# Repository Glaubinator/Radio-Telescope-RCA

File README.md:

# Radio-Telescope-RCA
Radio Telescope System for 1 GHz to 2 GHz Operation

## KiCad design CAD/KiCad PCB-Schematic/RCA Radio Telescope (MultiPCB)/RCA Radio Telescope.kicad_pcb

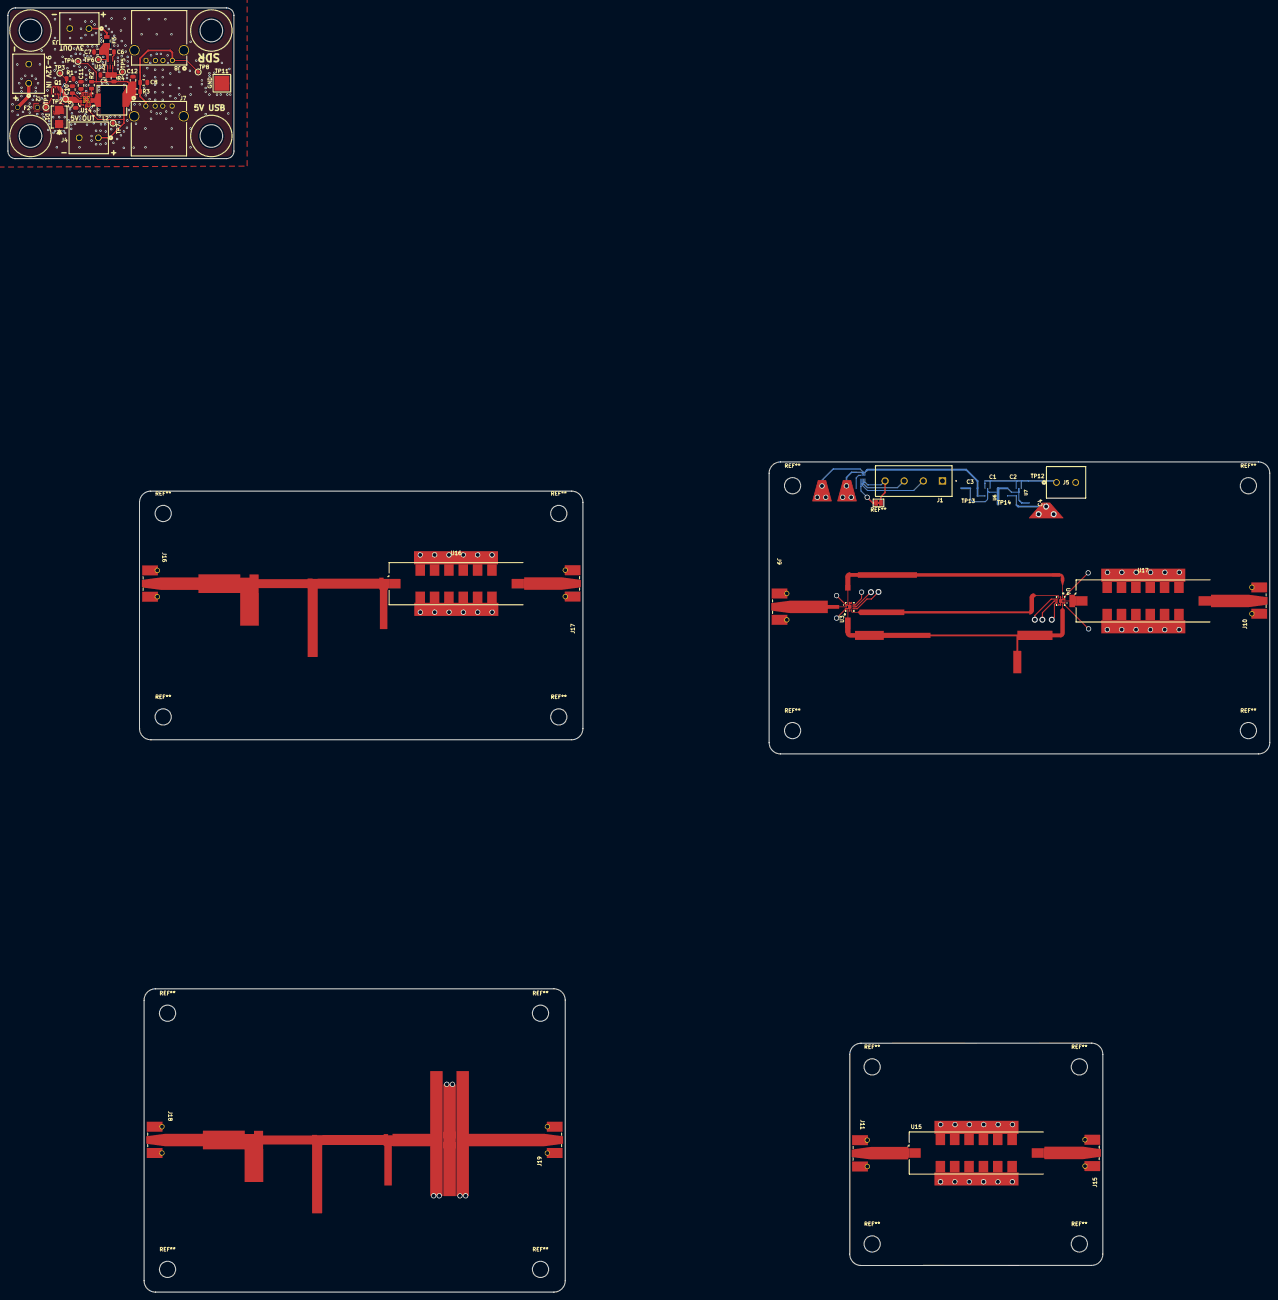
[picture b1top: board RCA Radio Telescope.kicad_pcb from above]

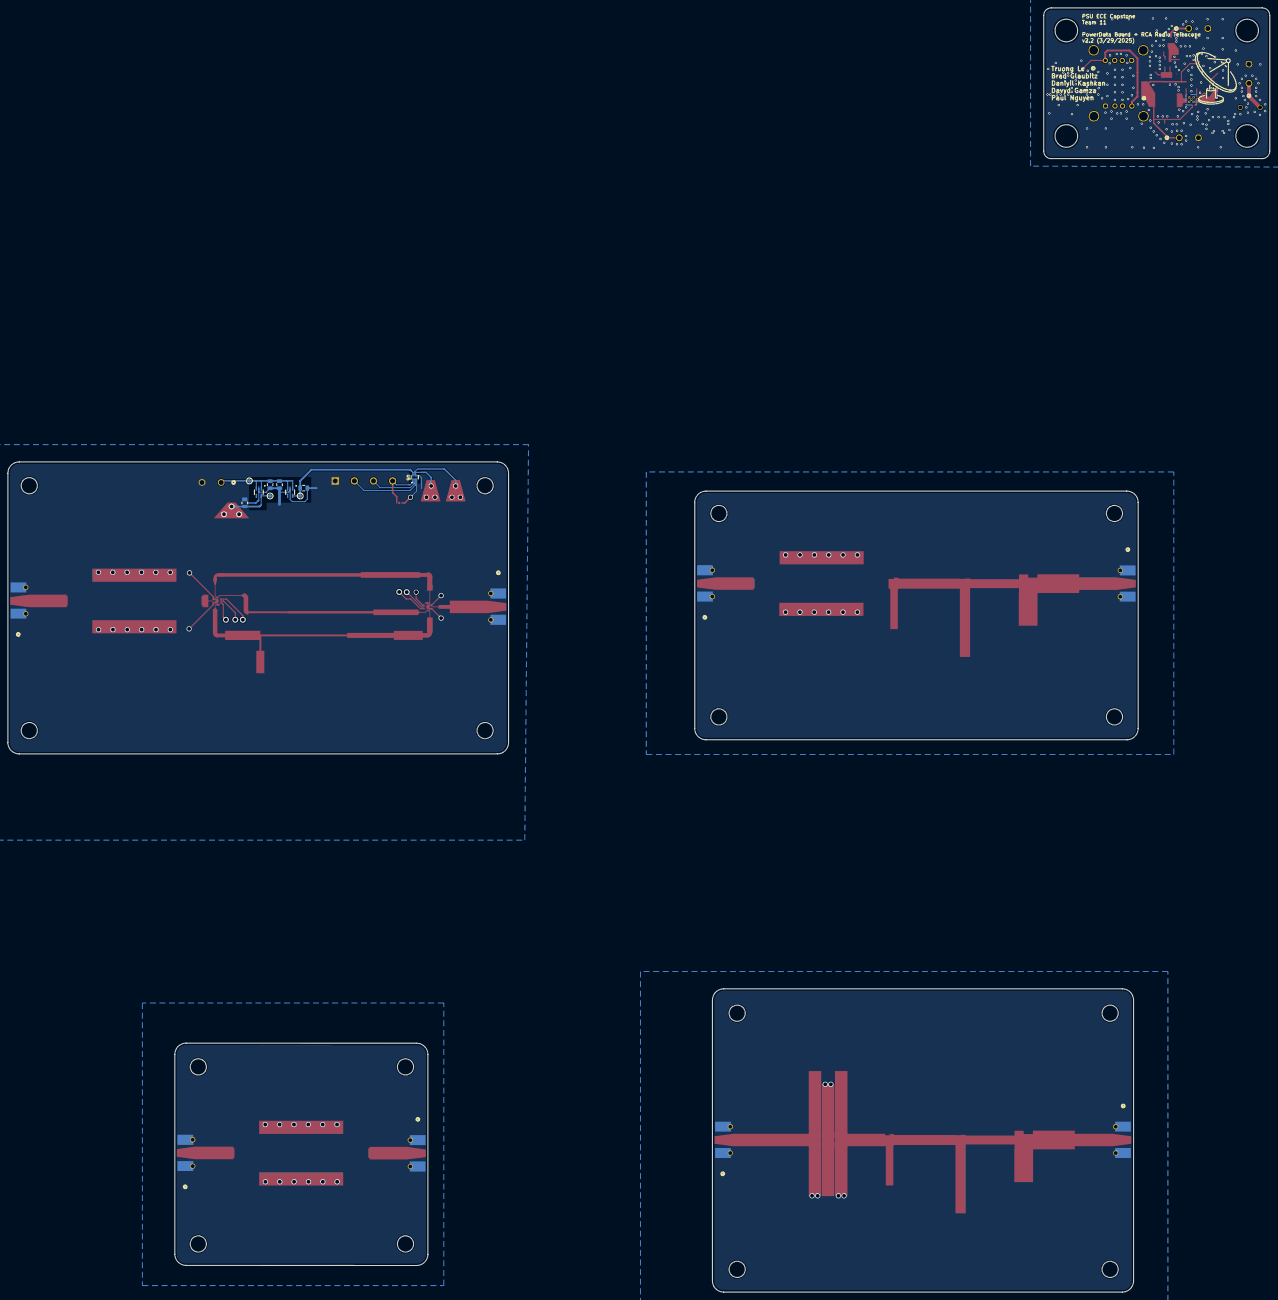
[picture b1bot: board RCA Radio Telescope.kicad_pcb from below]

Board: 2 copper layers, 335.0 x 340.9 mm, 63 parts (10 on the bottom side), 36 nets.

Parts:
C1, C2, C3, C4, C5, C7: 1 uF; C_0805_2012Metric
C6: 10 nf; C_0805_2012Metric
C8: 10 uF; C_0805_2012Metric
C9: 10uF; C_0805_2012Metric
C10: 0.1uF; C_0805_2012Metric
C11: 3.3nF; C_0805_2012Metric
C12: 22uF; C_0805_2012Metric
D1: SMBJ12A-13-F; SMB_DIO
F2: RGEF300K-2
F3: 0ZCK0020FF2G; 0ZCK_BEL
J1: Screw_Terminal_01x04; PHOENIX_1729144
J2: 9-12V From PoE Splitter; CONN_1729128_PXC
J3: 3V Out For LNA; CONN_1729128_PXC
J4: 5V Out For Filter Board; CONN_1729128_PXC
J5: 5V From SDR; CONN_1729128_PXC
J7, J8: USB_A; CONN_AU-Y1005-2_ASM
J9, J11, J15, J16, J17, J18, J19: ANT; CONN_142-0711-821_CIN
J10: FILTER_OUT; CONN_142-0711-821_CIN
L2: 2.2uH; IND_CB_DRA73
MDF: Kikit_Board_Label
MSF: Kikit_Board_Label
PD: Kikit_Board_Label
Q1: DMP4047LFDE-7; U-DFN2020-6_DIO
R1, R2: 100k; R_0805_2012Metric
R3, R4: 0; R_0805_2012Metric
RFS: Kikit_Board_Label
SF: Kikit_Board_Label
TP1: PROCTVIN; TestPoint_Pad_D1.0mm_Edit
TP2: 5VBUCKVIN; TestPoint_Pad_D1.0mm_Edit
TP3: G_PMOS; TestPoint_Pad_D1.0mm_Edit
TP4: 5VBUCKVOUT; TestPoint_Pad_D1.0mm_Edit
TP5: 3VLDOIN; TestPoint_Pad_D1.0mm_Edit
TP6: 3VLDOOUT; TestPoint_Pad_D1.0mm_Edit
TP7: 5VOUT; TestPoint_Pad_D1.0mm_Edit
TP8: 5VUSB; TestPoint_Pad_D1.0mm_Edit
TP11: GNDCLIP; TestPoint_Pad_4.0x4.0mm_Edit
TP12: FCTRL_VIN; TestPoint_Pad_D1.0mm_Edit
TP13: FCTRL_1V8; TestPoint_Pad_D1.0mm_Edit
TP14: FCTRL_3V3; TestPoint_Pad_D1.0mm_Edit
U3, U4: SKY13588-460LF; QFN12_SKY
U5: SN74AVC2T244DQER; SON35P140X100X40-8N
U6: MIC5365-1.8YC5-TR; SOT65P210X110-5N
U7: MIC5365-3.3YC5-TR; SOT65P210X110-5N
U13: MAX8510EXK30T; SOT65P210X110-5N
U14: TPS62133RGTR; RGT0016C
U15, U16: BPF-A1340+; Mini-Circuits_HQ1157
U17: BPF-A355; Mini-Circuits_HQ1157

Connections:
/Matched Distributive Filter/GND: J18.1 (In), J18.2 (Ext), J19.1 (In), J19.2 (Ext)
/Matched SMD Filter/GND: J16.2 (Ext), J17.2 (Ext), U16.2 (GND), U16.3 (GND), U16.4 (GND), U16.5 (GND), U16.6 (GND), U16.7 (GND), U16.9 (GND), U16.10 (GND), U16.11 (GND), U16.12 (GND), U16.13 (GND), U16.14 (GND)
/Matched SMD Filter/SIGNAL_IN: J16.1 (In), U16.1 (IN)
/Matched SMD Filter/SIGNAL_OUT: J17.1 (In), U16.8 (OUT)
/POWERDATA_GND: C5.2, C7.2, C8.2, C9.2, C10.2, C11.1, C12.2, D1.2, J2.2, J3.2, J4.2, J7.4 (GND), J8.4 (GND), R1.2, TP11.1, U13.2 (GND), U14.5 (FB), U14.6 (AGND), U14.7 (FSW), U14.8 (DEF), U14.15 (PGND), U14.16 (PGND), U14.17 (EP)
/PowerDataDistribute/VDD: F2.1, J2.1
/PowerDataDistribute/VOUT_3V: F3.2, J3.1
/PowerDataDistribute/VOUT_5V: C12.1, J4.1, L2.2, R2.1, R3.2, R4.2, TP4.1, TP7.1, U14.14 (VOS)
/RFS_GND: C1.2, C2.2, C3.1, C4.1, J1.1, J5.2, J9.2 (Ext), J10.2 (Ext), U3.2 (GND), U3.7 (GND), U3.8 (GND), U3.10 (GND), U3.12 (GND), U3.13 (EPAD), U4.2 (GND), U4.7 (GND), U4.8 (GND), U4.10 (GND), U4.12 (GND), U4.13 (EPAD), U5.5 (GND), U6.2 (GND), U7.2 (GND), U17.2 (GND), U17.3 (GND), U17.4 (GND), U17.5 (GND), U17.6 (GND), U17.7 (GND), U17.9 (GND), U17.10 (GND), U17.11 (GND), U17.12 (GND), U17.13 (GND), U17.14 (GND)
/RFSwitchFilter/5V_IN: C1.1, C2.1, J5.1, TP12.1, U6.1 (VIN), U6.3 (EN), U7.1 (VIN), U7.3 (EN)
/RFSwitchFilter/+1V8: C3.2, TP13.1, U5.8 (VCCB), U6.5 (VOUT)
/RFSwitchFilter/+3V3: C4.2, TP14.1, U3.6 (VDD), U4.6 (VDD), U7.5 (VOUT)
/RFSwitchFilter/ANT: J9.1 (In), U3.11 (RFC)
/RFSwitchFilter/CNTR_V1: J1.3, U5.2 (A1)
/RFSwitchFilter/CNTR_V2: J1.2, U5.3 (A2)
/RFSwitchFilter/FILTERA_IN: U3.1 (J1), U4.9 (J2)
/RFSwitchFilter/FILTERB_IN: U3.9 (J2), U4.1 (J1)
/RFSwitchFilter/FILTERC_IN: U3.3 (J3), U4.3 (J3)
/RFSwitchFilter/FILTER_OUT: J10.1 (In), U17.8 (OUT)
/RFSwitchFilter/INT_CTRL_V1: U3.4 (V1), U4.5 (V2), U5.7 (B1)
/RFSwitchFilter/INT_CTRL_V2: U3.5 (V2), U4.4 (V1), U5.6 (B2)
/RFSwitchFilter/VDD_REF: J1.4, U5.1 (VCCA), U5.4 (~OE)
/SMDFilter/GND: J11.2 (Ext), J15.2 (Ext), U15.2 (GND), U15.3 (GND), U15.4 (GND), U15.5 (GND), U15.6 (GND), U15.7 (GND), U15.9 (GND), U15.10 (GND), U15.11 (GND), U15.12 (GND), U15.13 (GND), U15.14 (GND)
/SMDFilter/SIGNAL_IN: J11.1 (In), U15.1 (IN)
/SMDFilter/SIGNAL_OUT: J15.1 (In), U15.8 (OUT)
unnamed: C8.1, J7.1 (VBUS), J8.1 (VBUS), R3.1, TP8.1
unnamed: L2.1, U14.1 (SW), U14.2 (SW), U14.3 (SW)
unnamed: D1.1, F2.2, Q1.1 (D), TP1.1
unnamed: Q1.2 (G), R1.1, TP3.1
unnamed: C9.1, C10.1, Q1.3 (S), TP2.1, U14.10 (AVIN), U14.11 (PVIN), U14.12 (PVIN), U14.13 (EN)
unnamed: C6.2, U13.4 (BP)
unnamed: C5.1, R4.1, TP5.1, U13.1 (IN), U13.3 (~SHDN)
unnamed: C6.1, C7.1, F3.1, TP6.1, U13.5 (OUT)
unnamed: R2.2, U14.4 (PG)
unnamed: C11.2, U14.9 (SS_TR)
unnamed: U4.11 (RFC), U17.1 (IN)

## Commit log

2024-12-31 Setting up repository
2024-12-31 Updating repository
2025-01-10 Rename RCA - Radio Telescope System for 1 GHz to 2 GHz Operation (NEW).pdf to RCA - Radio Telescope System for 1 GHz to 2 GHz Operation (01_02_2025).pdf
2025-01-10 Radio Telescope System for 1 GHz to 2 GHz Operation (UPDATED, 01_07_2025).pdf
2025-01-10 Rename RCA - Radio Telescope System for 1 GHz to 2 GHz Operation (UPDATED, 01_07_2025).pdf
2025-01-23 Adding empty folders
2025-01-24 Block Diagrams
2025-01-24 ECE412_Project Proposal_Radio Telescope_Team 11
2025-01-28 Updated Team 11 Project Proposal
2025-01-28 Updated Version Number
2025-02-01 Updated PDS Version 1.2
2025-02-02 Updated PDS Version 1.3
2025-02-02 Adding Datasheets
2025-02-02 Adding Decision Matrices
2025-02-02 Cleaning
2025-02-04 Finalized Project Proposal with signatures
2025-02-04 Fixed Date on Project Proposal
2025-02-04 Fully Signed Document
2025-02-08 V1 BOM
2025-02-09 Added LNA and Antenna
2025-02-10 Radio Telescope GanttChart V1.1
2025-02-10 Uploaded PDF Version of Gantt Chart V1.1
2025-02-10 Updated Schematic
    Added SDR, Battery (incomplete)
2025-02-12 Updated Schematic
    Updated schematic with buck board, and foundation for Power Over Ethernet.
2025-02-12 Updated Schematic to v1.1
    - Added PoE, Power Supply components
    - Laid out components on base side
    - Added details about voltages for PoE
    - Updated and added symbols for Pluto, Ethernet Dongle, PoE Injector/Splitter, and Boost Converter
2025-02-15 Revised BOM name for version control
2025-02-15 BOM V2 Updated
2025-02-22 V3 BOM
2025-02-24 Update Schematic to Version 1.2
    - Removed Buck Converter
    - Added Section for Step Down (need to find one that is good and can provide smooth voltage)
    - Added USB schematic symbols
2025-02-28 Updated Schematic
    Updated System Schematic to v1.3
    -Add Hierarchal Schematics for Filters and Power/Data Distribution
    Updated Filters Schematic to v1.0
    - Added circuitry for RF switching, level shifting, and power supply.
    - Added placeholders for filters
    Updated Power/Data Distribution Schematic to v1.0
2025-03-01 V4 BOM
2025-03-01 Updated Filter Select Script to v1.0
2025-03-01 Updated Filter Select Script to v1.1
2025-03-05 Updated Schematic
    Updated Root Schematic to v1.4
    - Added Screw Terminals for 5V In/Out, 3V Out for LNA
    - Reorganized Skylark Shed Power to include Battery, Inverter, and AC-DC Adapter
    - Added TODO list
    Updated PowerDataDistribute Schematic to v1.1
    - Removed labels for USB signals and replaced it with single USB_OUT signal
2025-03-06 Updated Schematic
    Updated Root Schematic to v1.5, Filters to v1.1, and PowerDataDistribute to v1.1.
    - Updated part references to be more consistent
    - Added missing GND label for SDR GPO
2025-03-07 Updated Filter Schematic to v1.2
    - Fixed switch logic to better suit the footprint layout (Swapped J1 and J2 on one switch (secondary one) and swapped the v1 and v2 pins on the same switch)
2025-03-14 Updated PowerDataDistribute Schematic to v1.3
    - Added 5V to 3V Buck for LNA
    - Added TVS diode, PMOS, and polyfuse for power protection (need to select PMOS and polyfuse)
2025-03-16 v5 BOM
2025-03-16 Updated PowerDataDistribute schematicto v1.4
    - Added components for fuses and PMOS
    - Created PCB v1.0
2025-03-16 Updated Power/Data Distribute Board to v1.1
    - Adjusted screw hole positions
    - Adjusted screw terminal positions
2025-03-17 BOM Update and Schematic Update
2025-03-17 Fixed Double Counting on BOM
2025-03-22 Updated PowerData Board to v1.2
    - Added zone fills for certain pins
    - Added ground vias for mounting holes
    - Minor readjustments to components
    - Added silkscreen for voltage polarity
2025-03-25 Updated Power Data Distribute PCB to v1.3
    - Rearranged 5 to 3V PCB layout to fit new circuit
    - Added via stitching to PCB
    - Added some constraints supplied by JLCPCB
2025-03-25 V1.5 Schematic and 1.4 PCB Layout
2025-03-25 Updated Power/Data Schematic to v1.6 and Power/Data PCB to v1.5
    - Added Testpoints to both Schematic and PCB
    - Rearranged components on PCB to fit missing diode
    - Changed Zener diode and PMOS on Protection Circuit to work with 12V max
    - Fixed warnings and errors from DRC
2025-03-26 Updated PowerData PCB to v1.6 and PowerData Schematic to v1.7
    - Design Review with Andrew
    - Fixed up various parts of PCB parameters
    - May consider LDO or filtering for Power IC
    - May want to consider a circuit breaker IC for LNA supply
2025-03-28 Updated PowerData Schematic to v1.8 and PCB to v1.7
    - Swapped MIC Buck to LDO
    - Changed footprint for Buck Inductor to appropriate component
    - Rearranged PCB layout to accommodate new inductor
2025-03-28 Updated PowerData Schematic to v1.9 and PCB to v1.8
    - Swapped LDO (Obsolete) with an Active version in both Schematic and PCB
2025-03-28 small adjustment to boardsetup
    only changed one thing called min connection width from 0 -> 0.1mm on board setup
2025-03-29 Updated PowerData Schematic to v2.0 and PCB to v1.9
    - Added 0 Ohm resistors to modularized PCB
    - Adjusted some GND vias to prevent clipping of silkscreen
    - Edited LDO footprint to adhere with JLC specs
2025-03-29 Create Flange
2025-03-29 Updated PowerData PCB to v2.0
    - Readjusted some via holes and grounding for Buck
    - Adjusted location for testpoint and silkscreens
2025-03-29 Updated PowerData PCB to v2.1
    - Added custom JLC rules from https://github.com/Cimos/KiCad-CustomDesignRules/tree/main
    - Adjusted silkscreen according to new rules
    - Added step models for components
    - Adjusted via locations to be more spread out
2025-03-29 Updated Root Schematic to v1.6 and P/D PCB to v2.2
    - Changed input voltage to P/D board to 9-12V (Concerned about voltage drop of components which may not allow for 5V out)
2025-03-30 Rename Gerber Zip
2025-03-31 KiKit Integration and Multi Schematic Updates
    Updated Root Schematic to V1.7 (Major Changes)
    - Needed to remove all global power symbols in every schematic/sub-schematic to use KiKit's MultiPCB workflow
    - Changed them to local labels
    Added Filters V1 and FiltersCTRL V1.4
    - Separated Filter Board into two schematics: Filters and FIltersCTRL
    - Continued revision number from former Filters schematic to FiltersCTRL
2025-04-02 V8 BOM
2025-04-02 Added KiKit Board Designators to PCB editor and Library
2025-04-03 Fixed Slight Mistake
    No revision necessary
2025-04-04 Update to Schematic and PCB
    Filter Control Schematic to v1.5
    - Removed redundant connector symbol
    Root Schematic to v1.9
    - Adjusted pin connections for J14 and J14
    Created Matching Network PCB
    - Filter Board Schematic renamed to MatchNetwork
2025-04-04 Updated FC board to v1.1
    - Removed some vias to reduce required time to solder them
    - Adjusted via size to 0.4 to meet EPL specs
    -Exported as FC_V1-1 in Kikit exports
    Updated Kikit Example
    - Added a step guide on how to use tool
    - Will make a Git Wiki once done
2025-04-08 Update SMD Filter PCB to v1.0
    - Imported ADS layout for SMD filter to KiCAD PCB file
    - Added footprint for MiniCircuit Filter
2025-04-09 Updated Schematics and PCBs
    Root Schematic to v2.0
    - Swapped Matching Network segment for SMD filter
    - Updated TODO list
    SMD Filter PCB to v1.0
    - Added filter and SMA connector footprints
    - Imported ADS trace layout
2025-04-09 Updated SMD Filter PCB to v1.1
    - Adjusted GND pads from 10 to 6mm
    - Added M4 Holes for mounting
2025-04-09 Updated SMD FIlter Board to v1.2
    - Added KiKit Label
    - Minor adjustments to PCB
    - Exported to separate project
    - Edited SMA connector footprint
2025-04-10 Add Measurement Text for Boards
2025-04-11 Updated SMD FIlter Board to v1.3
    - Adjusted line length to remove 39 ohm segment
    - Updated screwholes to be correct size
2025-04-12 Updated BOM to Rev 10
2025-04-18 Create Files
2025-04-26 Add 1.6 GHZ Matching Network PCB v1.0
    - Same design as original board, but with 1.6 GHz matching network
2025-04-26 Added Coupled Lines Filter PCB v1.0 and Exported PD Board Step File
2025-04-28 Team 11 Test Plan added to Project Info
2025-04-29 RF Boards Redo (WIP)
    - Overhauling current RF boards to keep 4 RF boards in total
2025-04-30 Added 4 RF Board Designs into KiCAD project
    - Added Matched SMD Filter Board, Matched Distributive Filter Board, RF Switch Filter Board, and kept original SMD Filter Board
2025-04-30 Updated PCB size for RF boards, and relocated power circuitry for RF switch board
2025-05-02 Update RF Board Designs
    - Added Vias to SMA connector pads
    - Removed wiring for control/power wires for RF switches
    - Adjusted grounding for RF filters
2025-05-05 Updated RF Board Hole Data and Exported STEPs for 3D Modeling
2025-05-06 Added SMA Models to Step Files
2025-05-07 Added Extra Pads and Adjust Layout
    Updated RFS PCB to v1.4
2025-05-10 Update Level 0 and Level 1.png
    Update of Level 0 and Level 1 from V3 to V4/
2025-05-23 Create file
2025-05-24 Update Level 0 and Level 1.png
    L0 and L1 filters updated
2025-05-28 BOM Revision 11
2025-05-28 Bom Rev 11 PDF
2025-06-06 Updated Simulations
2025-06-06 Uploading Simulations and Measurements
2025-06-11 Updated Schematic to Fix USB/PMOS issues and Minor Fixes
2025-06-16 Removed empty files
